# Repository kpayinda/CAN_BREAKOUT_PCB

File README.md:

# CAN Bus Development Board

A general-purpose breakout and development board featuring the **MCP2562FDT** CAN transceiver, designed for testing and system integration.

## Key Features
* **Transceiver:** MCP2562FDT-E/SN (supports CAN FD up to 5 Mbps).
* **Power Rails:** Dual-rail design ($V_{DD} = 5\text{V}$ for bus, $V_{IO} = 3.3\text{V}$ for logic compatibility).
* **Protection:** On-board TVS diodes for ESD protection and space for a Common-Mode Choke.
* **Termination:** Includes optional split termination ($2 \times 60\,\Omega$ with a center-tapped capacitor to GND).

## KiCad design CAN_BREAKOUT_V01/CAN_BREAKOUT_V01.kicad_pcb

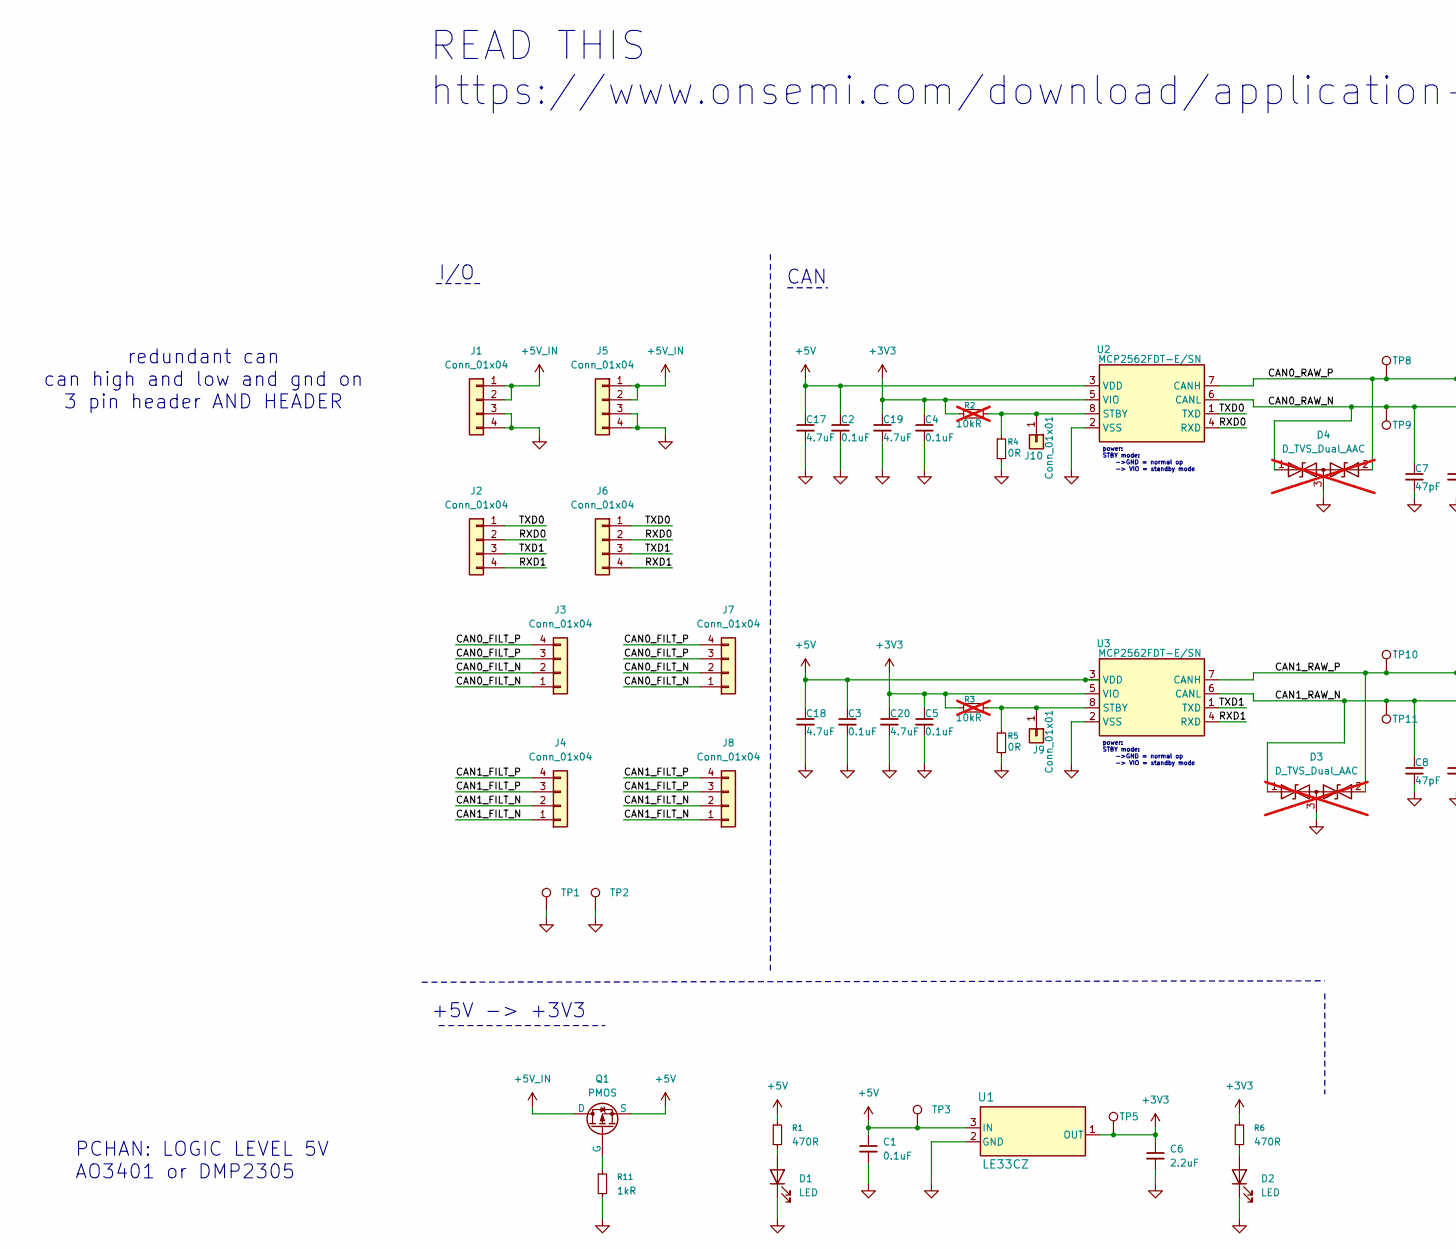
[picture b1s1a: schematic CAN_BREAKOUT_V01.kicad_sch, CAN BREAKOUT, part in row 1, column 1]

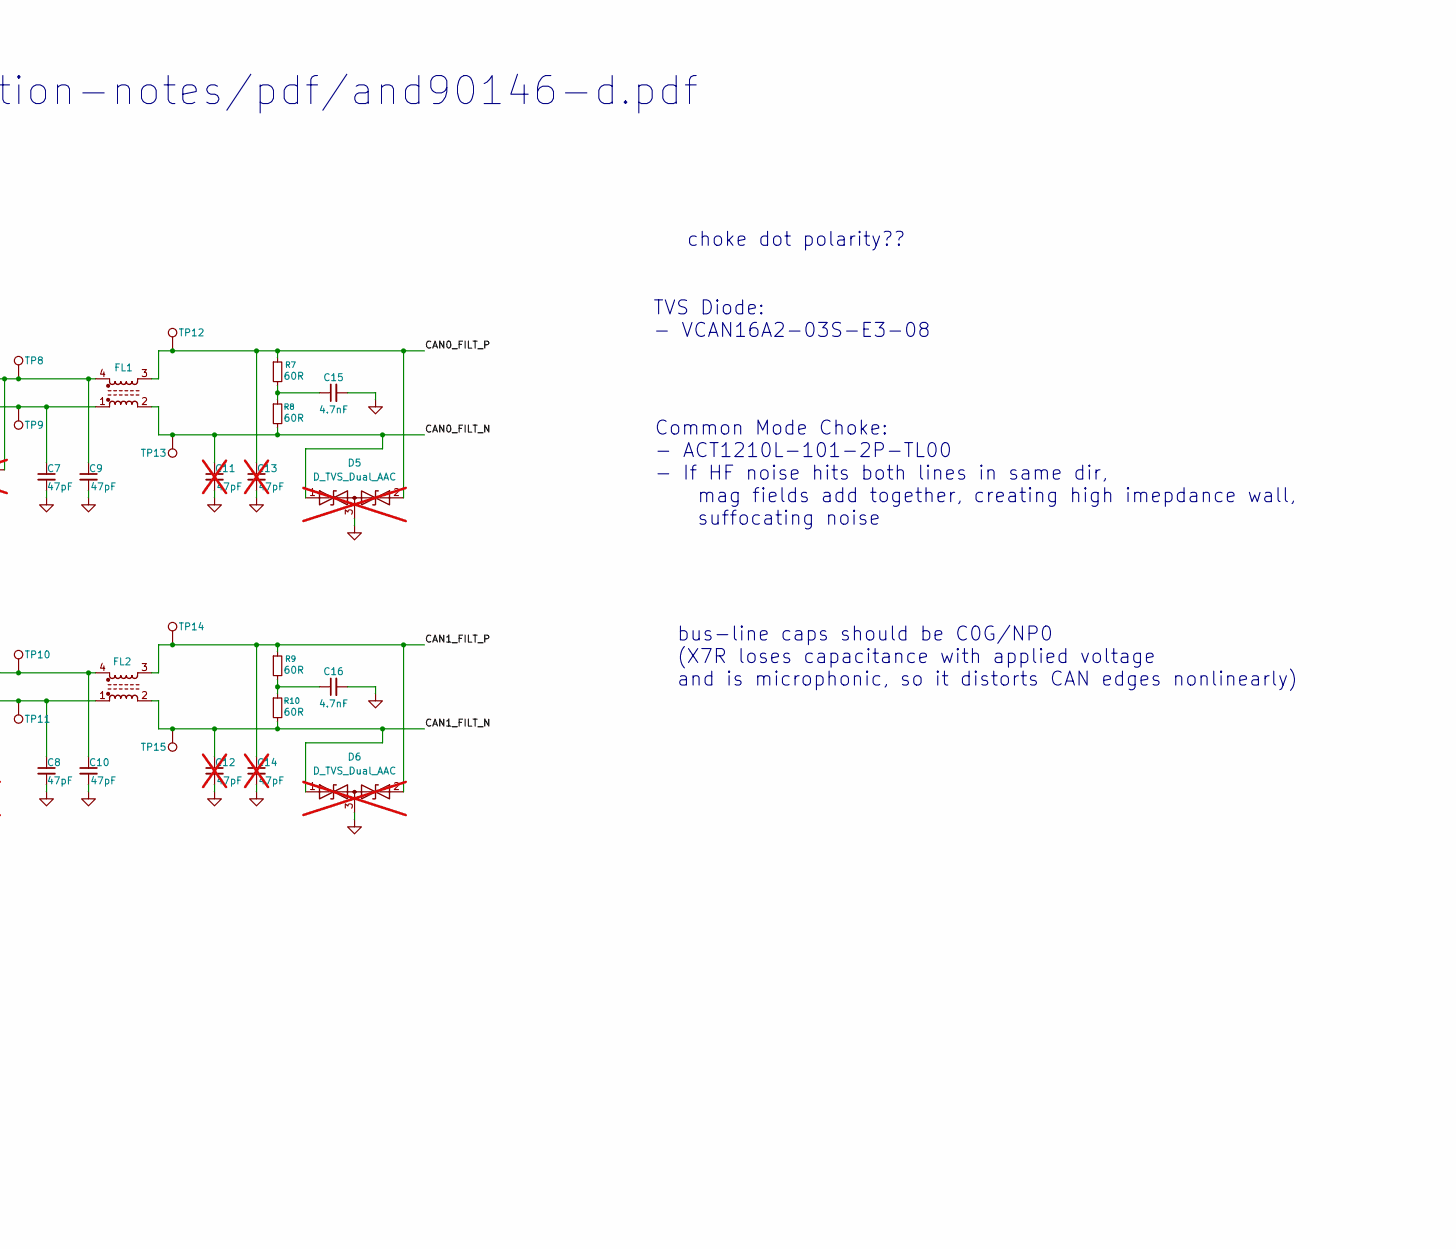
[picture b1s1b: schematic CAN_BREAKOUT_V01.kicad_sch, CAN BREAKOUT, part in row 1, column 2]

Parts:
C1, C2, C3, C4, C5: 0.1uF; C_0603_1608Metric
C6: 2.2uF; C_0603_1608Metric
C7, C8, C9, C10: 47pF; C_0603_1608Metric
C11, C12, C13, C14: 47pF; C_0603_1608Metric; not fitted
C15, C16: 4.7nF; C_0603_1608Metric
C17, C18, C19, C20: 4.7uF; C_0603_1608Metric
D1, D2: LED; LED_0603_1608Metric
D3, D4, D5, D6: D_TVS_Dual_AAC; SOT-23-3; not fitted
FL1, FL2: Choke_CommonMode_FerriteCore_1243; L_CommonModeChoke_Coilcraft_1812CAN
J1, J2, J7, J8: Conn_01x04; Molex_PicoBlade_53261-0471_1x04-1MP_P1.25mm_Horizontal
J3, J4, J5, J6: Conn_01x04; PinHeader_1x04_P2.54mm_Vertical
J9, J10: Conn_01x01; PinHeader_1x01_P2.54mm_Vertical
Q1: PMOS; SOT-23-3
R1, R6: 470R; R_0603_1608Metric
R2, R3: 10kR; R_0603_1608Metric; not fitted
R4, R5: 0R; R_0603_1608Metric
R7, R8, R9, R10: 60R; R_0603_1608Metric
R11: 1kR; R_0603_1608Metric
TP1, TP2, TP3, TP5, TP8, TP9, TP10, TP11, TP12, TP13, TP14, TP15: TestPoint; TestPoint_Keystone_5000-5004_Miniature
U1: LE33CZ; TO-92
U2, U3: MCP2562FDT-E/SN; SOIC-8_3.9x4.9mm_P1.27mm

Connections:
+3V3: C4.1, C5.1, C6.1, C19.1, C20.1, R2.2, R3.2, R6.1, TP5.1, U1.1 (OUT), U2.5 (VIO), U3.5 (VIO)
+5V: C1.1, C2.1, C3.1, C17.1, C18.1, Q1.3 (S), R1.1, TP3.1, U1.3 (IN), U2.3 (VDD), U3.3 (VDD)
+5V_IN: J1.1, J1.2, J5.1, J5.2, Q1.1 (D)
/CAN0_FILT_N: C11.1, D5.1 (A1), FL1.2, J3.1, J3.2, J7.1, J7.2, R8.2, TP13.1
/CAN0_FILT_P: C13.1, D5.2 (A2), FL1.3, J3.3, J3.4, J7.3, J7.4, R7.1, TP12.1
/CAN0_RAW_N: C7.1, D4.1 (A1), FL1.1, TP9.1, U2.6 (CANL)
/CAN0_RAW_P: C9.1, D4.2 (A2), FL1.4, TP8.1, U2.7 (CANH)
/CAN1_FILT_N: C12.1, D6.1 (A1), FL2.2, J4.1, J4.2, J8.1, J8.2, R10.2, TP15.1
/CAN1_FILT_P: C14.1, D6.2 (A2), FL2.3, J4.3, J4.4, J8.3, J8.4, R9.1, TP14.1
/CAN1_RAW_N: C8.1, D3.1 (A1), FL2.1, TP11.1, U3.6 (CANL)
/CAN1_RAW_P: C10.1, D3.2 (A2), FL2.4, TP10.1, U3.7 (CANH)
/RXD0: J2.2, J6.2, U2.4 (RXD)
/RXD1: J2.4, J6.4, U3.4 (RXD)
/TXD0: J2.1, J6.1, U2.1 (TXD)
/TXD1: J2.3, J6.3, U3.1 (TXD)
GND: C1.2, C2.2, C3.2, C4.2, C5.2, C6.2, C7.2, C8.2, C9.2, C10.2, C11.2, C12.2, C13.2, C14.2, C15.2, C16.2, C17.2, C18.2, C19.2, C20.2, D1.1 (K), D2.1 (K), D3.3 (common), D4.3 (common), D5.3 (common), D6.3 (common), J1.3, J1.4, J5.3, J5.4, R4.2, R5.2, R11.2, TP1.1, TP2.1, U1.2 (GND), U2.2 (VSS), U3.2 (VSS)
unnamed: C15.1, R7.2, R8.1
unnamed: C16.1, R9.2, R10.1
unnamed: D1.2 (A), R1.2
unnamed: D2.2 (A), R6.2
unnamed: J9.1, R3.1, R5.1, U3.8 (STBY)
unnamed: J10.1, R2.1, R4.1, U2.8 (STBY)
unnamed: Q1.2 (G), R11.1

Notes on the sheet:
power: STBY mode: ->GND = normal op -> VIO = standby mode
READ THIS https://www.onsemi.com/download/application-notes/pdf/and90146-d.pdf
PCHAN: LOGIC LEVEL 5V AO3401 or DMP2305
Common Mode Choke: - ACT1210L-101-2P-TL00 - If HF noise hits both lines in same dir, mag fields add together, creating high imepdance wall, suffocating noise
I/O
CAN
choke dot polarity??
bus-line caps should be C0G/NP0 (X7R loses capacitance with applied voltage and is microphonic, so it distorts CAN edges nonlinearly)
+5V -> +3V3
TVS Diode: - VCAN16A2-03S-E3-08
redundant can can high and low and gnd on 3 pin header AND HEADER

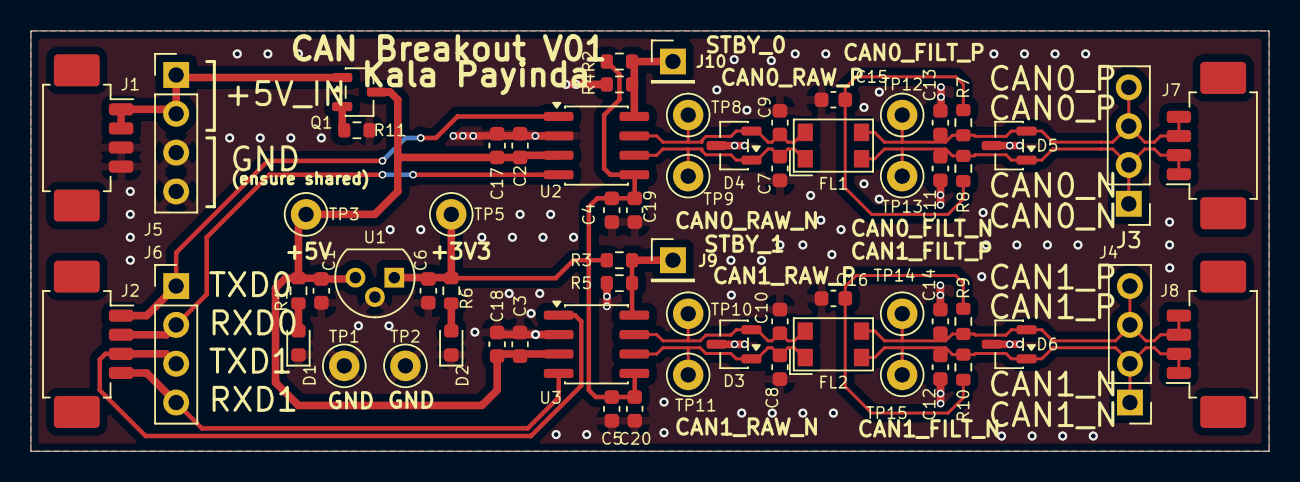
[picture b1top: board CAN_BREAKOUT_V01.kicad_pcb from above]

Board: 2 copper layers, 81.0 x 27.5 mm, 65 parts (0 on the bottom side), 23 nets.

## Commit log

2026-06-04 Init
2026-06-04 pre-reviewed PCB
2026-06-04 Fix gitignore extension and untrack backup junk files
2026-06-04 cleaning
2026-06-04 added pcb files
2026-06-17 updated to break out SYNC pin to enable MCU control of redundancy channel; still getting text warnings, dont know how to change rules yet..
2026-06-18 ordering this V01 through JLCPCB
